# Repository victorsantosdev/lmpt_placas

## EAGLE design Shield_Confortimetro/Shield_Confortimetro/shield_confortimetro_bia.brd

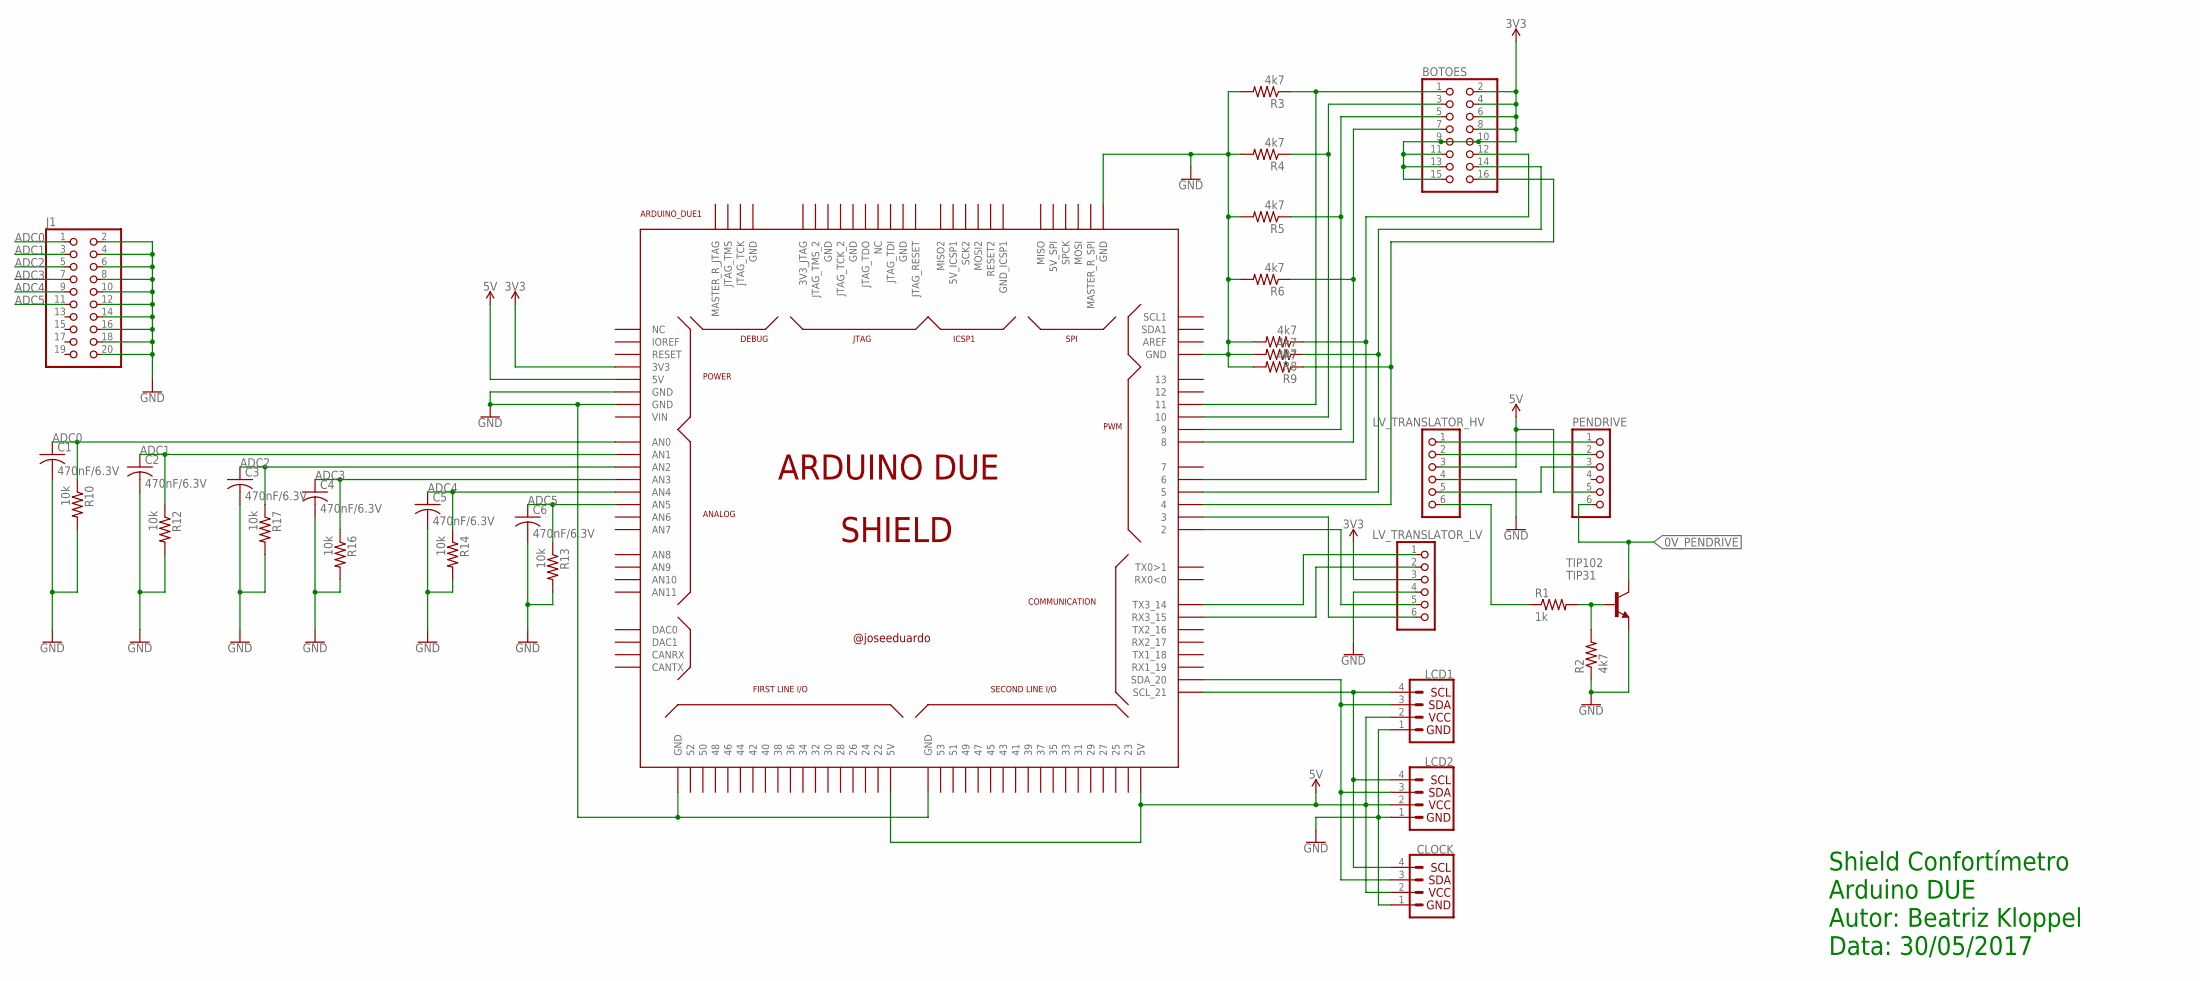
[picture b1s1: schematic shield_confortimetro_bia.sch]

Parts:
ARDUINO_DUE1: ARDUINO_DUE_SHIELD
BOTOES: PINHD-2X8; 2X08
C1, C2, C3, C4, C5, C6: 470nF/6.3V; C050-030X075
CLOCK: I2C_STANDARD; 1X04
J1: PINHD-2X10; 2X10
LCD1, LCD2: I2C_STANDARD; 1X04
LV_TRANSLATOR_HV: PINHD-1X6; 1X06
LV_TRANSLATOR_LV: PINHD-1X6; 1X06
PENDRIVE: PINHD-1X6; 1X06
R1: 1k; 0309/12
R2, R3, R4, R5, R6, R7, R8, R9: 4k7; 0309/12
R10, R12, R13, R14, R16, R17: 10k; 0309/12
TIP102: TIP31; TO220

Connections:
0V_PENDRIVE: PENDRIVE.6, TIP102.2 (C)
ADC0: ARDUINO_DUE1.A0 (AN0), C1.1, J1.1, R10.1
ADC1: ARDUINO_DUE1.A1 (AN1), C2.1, J1.3, R12.1
ADC2: ARDUINO_DUE1.A2 (AN2), C3.1, J1.5, R17.1
ADC3: ARDUINO_DUE1.A3 (AN3), C4.1, J1.7, R16.1
ADC4: ARDUINO_DUE1.A4 (AN4), C5.1, J1.9, R14.1
ADC5: ARDUINO_DUE1.A5 (AN5), C6.1, J1.11, R13.1
GND: ARDUINO_DUE1.GND, ARDUINO_DUE1.GND_1 (GND), ARDUINO_DUE1.GND_2 (GND), ARDUINO_DUE1.GND_3 (GND), ARDUINO_DUE1.GND_4 (GND), ARDUINO_DUE1.GND_5 (GND), C1.2, C2.2, C3.2, C4.2, C5.2, C6.2, CLOCK.1, J1.2, J1.4, J1.6, J1.8, J1.10, J1.12, J1.14, J1.16, J1.18, J1.20, LCD1.1, LCD2.1, LV_TRANSLATOR_HV.4, LV_TRANSLATOR_LV.4, R2.1, R3.2, R4.2, R5.2, R6.2, R7.2, R8.2, R9.2, R10.2, R12.2, R13.2, R14.2, R16.2, R17.2, TIP102.3 (E)
unnamed: ARDUINO_DUE1.20 (SDA_20), CLOCK.3, LCD1.3, LCD2.3
unnamed: ARDUINO_DUE1.21 (SCL_21), CLOCK.4, LCD1.4, LCD2.4
unnamed: ARDUINO_DUE1.14 (TX3_14), LV_TRANSLATOR_LV.1
unnamed: ARDUINO_DUE1.15 (RX3_15), LV_TRANSLATOR_LV.2
unnamed: ARDUINO_DUE1.3, LV_TRANSLATOR_LV.6
unnamed: ARDUINO_DUE1.2, LV_TRANSLATOR_LV.5
unnamed: LV_TRANSLATOR_HV.1, PENDRIVE.1
unnamed: LV_TRANSLATOR_HV.2, PENDRIVE.2
unnamed: LV_TRANSLATOR_HV.5, PENDRIVE.3
unnamed: R1.2, R2.2, TIP102.1 (B)
unnamed: LV_TRANSLATOR_HV.6, R1.1
unnamed: ARDUINO_DUE1.6, BOTOES.12, R7.1
unnamed: ARDUINO_DUE1.5, BOTOES.14, R8.1
unnamed: ARDUINO_DUE1.4, BOTOES.16, R9.1
unnamed: ARDUINO_DUE1.8, BOTOES.7, R6.1
unnamed: ARDUINO_DUE1.9, BOTOES.5, R5.1
unnamed: ARDUINO_DUE1.10, BOTOES.3, R4.1
unnamed: ARDUINO_DUE1.11, BOTOES.1, R3.1
VCC_3V3: ARDUINO_DUE1.3V3, BOTOES.2, BOTOES.4, BOTOES.6, BOTOES.8, BOTOES.9, BOTOES.10, BOTOES.11, BOTOES.13, BOTOES.15, LV_TRANSLATOR_LV.3
VCC_5V: ARDUINO_DUE1.5V0 (5V), ARDUINO_DUE1.5V0_1 (5V), ARDUINO_DUE1.5V0_2 (5V), CLOCK.2, LCD1.2, LCD2.2, LV_TRANSLATOR_HV.3, PENDRIVE.5

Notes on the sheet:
Shield Confortímetro Arduino DUE Autor: Beatriz Kloppel Data: 30/05/2017

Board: 2 copper layers, 31 parts (9 on the bottom side), 28 nets, no tracks yet.

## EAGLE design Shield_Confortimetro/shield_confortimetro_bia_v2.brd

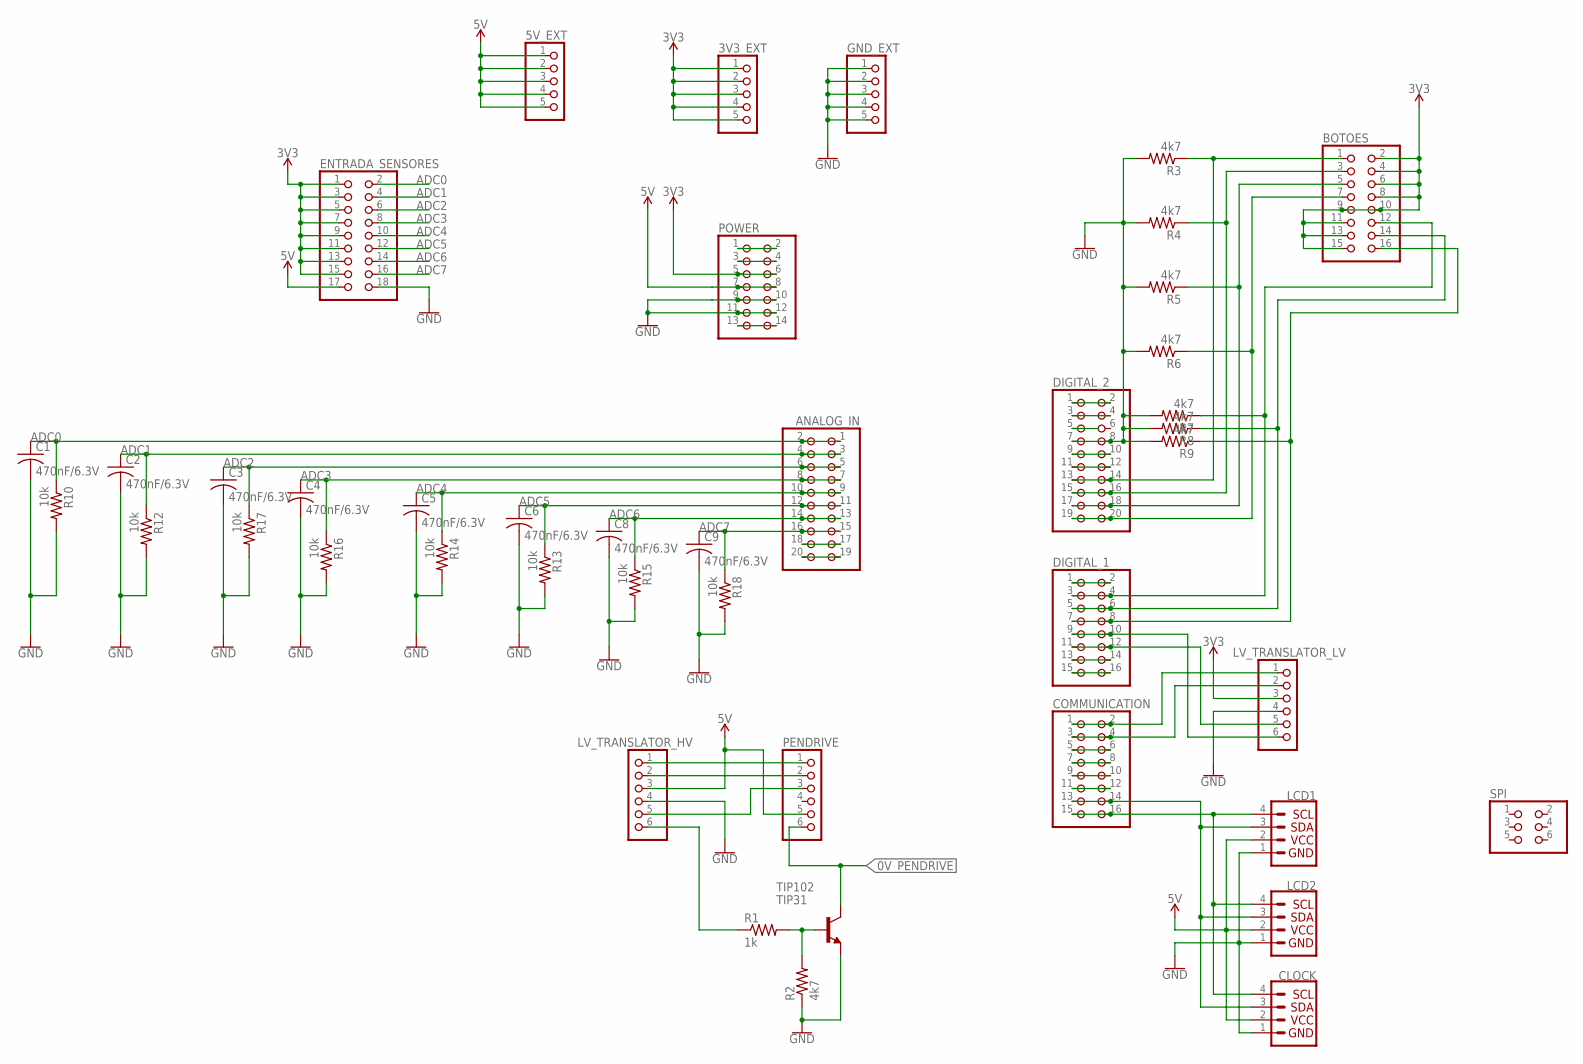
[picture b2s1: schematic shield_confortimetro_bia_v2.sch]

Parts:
3V3_EXT, 5V_EXT: PINHD-1X5; 1X05
ANALOG_IN: PINHD-2X10; 2X10
BOTOES: PINHD-2X8; 2X08
C1, C2, C3, C4, C5, C6, C8, C9: 470nF/6.3V; C050-030X075
CLOCK: I2C_STANDARD; 1X04
COMMUNICATION: PINHD-2X8; 2X08
DIGITAL_1: PINHD-2X8; 2X08
DIGITAL_2: PINHD-2X10; 2X10
ENTRADA_SENSORES: PINHD-2X9; 2X09
GND_EXT: PINHD-1X5; 1X05
LCD1, LCD2: I2C_STANDARD; 1X04
LV_TRANSLATOR_HV: PINHD-1X6; 1X06
LV_TRANSLATOR_LV: PINHD-1X6; 1X06
PENDRIVE: PINHD-1X6; 1X06
POWER: PINHD-2X7; 2X07
R1: 1k; 0309/12
R2, R3, R4, R5, R6, R7, R8, R9: 4k7; 0309/12
R10, R12, R13, R14, R15, R16, R17, R18: 10k; 0309/12
SPI: PINHD-2X3; 2X03
TIP102: TIP31; TO220

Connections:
0V_PENDRIVE: PENDRIVE.6, TIP102.2 (C)
ADC0: ANALOG_IN.1, ANALOG_IN.2, C1.1, ENTRADA_SENSORES.2, R10.1
ADC1: ANALOG_IN.3, ANALOG_IN.4, C2.1, ENTRADA_SENSORES.4, R12.1
ADC2: ANALOG_IN.5, ANALOG_IN.6, C3.1, ENTRADA_SENSORES.6, R17.1
ADC3: ANALOG_IN.7, ANALOG_IN.8, C4.1, ENTRADA_SENSORES.8, R16.1
ADC4: ANALOG_IN.9, ANALOG_IN.10, C5.1, ENTRADA_SENSORES.10, R14.1
ADC5: ANALOG_IN.11, ANALOG_IN.12, C6.1, ENTRADA_SENSORES.12, R13.1
ADC6: ANALOG_IN.13, ANALOG_IN.14, C8.1, ENTRADA_SENSORES.14, R15.1
ADC7: ANALOG_IN.15, ANALOG_IN.16, C9.1, ENTRADA_SENSORES.16, R18.1
GND: C1.2, C2.2, C3.2, C4.2, C5.2, C6.2, C8.2, C9.2, CLOCK.1, DIGITAL_2.7, DIGITAL_2.8, ENTRADA_SENSORES.18, GND_EXT.1, GND_EXT.2, GND_EXT.3, GND_EXT.4, GND_EXT.5, LCD1.1, LCD2.1, LV_TRANSLATOR_HV.4, LV_TRANSLATOR_LV.4, POWER.9, POWER.10, POWER.11, POWER.12, R2.1, R3.2, R4.2, R5.2, R6.2, R7.2, R8.2, R9.2, R10.2, R12.2, R13.2, R14.2, R15.2, R16.2, R17.2, R18.2, TIP102.3 (E)
unnamed: CLOCK.3, COMMUNICATION.13, COMMUNICATION.14, LCD1.3, LCD2.3
unnamed: CLOCK.4, COMMUNICATION.15, COMMUNICATION.16, LCD1.4, LCD2.4
unnamed: COMMUNICATION.1, COMMUNICATION.2, LV_TRANSLATOR_LV.1
unnamed: COMMUNICATION.3, COMMUNICATION.4, LV_TRANSLATOR_LV.2
unnamed: DIGITAL_1.9, DIGITAL_1.10, LV_TRANSLATOR_LV.6
unnamed: DIGITAL_1.11, DIGITAL_1.12, LV_TRANSLATOR_LV.5
unnamed: LV_TRANSLATOR_HV.1, PENDRIVE.1
unnamed: LV_TRANSLATOR_HV.2, PENDRIVE.2
unnamed: LV_TRANSLATOR_HV.5, PENDRIVE.3
unnamed: R1.2, R2.2, TIP102.1 (B)
unnamed: LV_TRANSLATOR_HV.6, R1.1
unnamed: BOTOES.12, DIGITAL_1.3, DIGITAL_1.4, R7.1
unnamed: BOTOES.14, DIGITAL_1.5, DIGITAL_1.6, R8.1
unnamed: BOTOES.16, DIGITAL_1.7, DIGITAL_1.8, R9.1
unnamed: BOTOES.7, DIGITAL_2.19, DIGITAL_2.20, R6.1
unnamed: BOTOES.5, DIGITAL_2.17, DIGITAL_2.18, R5.1
unnamed: BOTOES.3, DIGITAL_2.15, DIGITAL_2.16, R4.1
unnamed: BOTOES.1, DIGITAL_2.13, DIGITAL_2.14, R3.1
unnamed: POWER.1, POWER.2
unnamed: POWER.3, POWER.4
unnamed: POWER.13, POWER.14
unnamed: DIGITAL_2.1, DIGITAL_2.2
unnamed: DIGITAL_2.3, DIGITAL_2.4
unnamed: DIGITAL_2.9, DIGITAL_2.10
unnamed: DIGITAL_2.11, DIGITAL_2.12
unnamed: DIGITAL_1.1, DIGITAL_1.2
unnamed: DIGITAL_1.13, DIGITAL_1.14
unnamed: DIGITAL_1.15, DIGITAL_1.16
unnamed: COMMUNICATION.5, COMMUNICATION.6
unnamed: COMMUNICATION.7, COMMUNICATION.8
unnamed: COMMUNICATION.9, COMMUNICATION.10
unnamed: COMMUNICATION.11, COMMUNICATION.12
unnamed: ANALOG_IN.17, ANALOG_IN.18
unnamed: ANALOG_IN.19, ANALOG_IN.20
VCC_3V3: 3V3_EXT.1, 3V3_EXT.2, 3V3_EXT.3, 3V3_EXT.4, 3V3_EXT.5, BOTOES.2, BOTOES.4, BOTOES.6, BOTOES.8, BOTOES.9, BOTOES.10, BOTOES.11, BOTOES.13, BOTOES.15, ENTRADA_SENSORES.1, ENTRADA_SENSORES.3, ENTRADA_SENSORES.5, ENTRADA_SENSORES.7, ENTRADA_SENSORES.9, ENTRADA_SENSORES.11, ENTRADA_SENSORES.13, ENTRADA_SENSORES.15, LV_TRANSLATOR_LV.3, POWER.5, POWER.6
VCC_5V: 5V_EXT.1, 5V_EXT.2, 5V_EXT.3, 5V_EXT.4, 5V_EXT.5, CLOCK.2, ENTRADA_SENSORES.17, LCD1.2, LCD2.2, LV_TRANSLATOR_HV.3, PENDRIVE.5, POWER.7, POWER.8

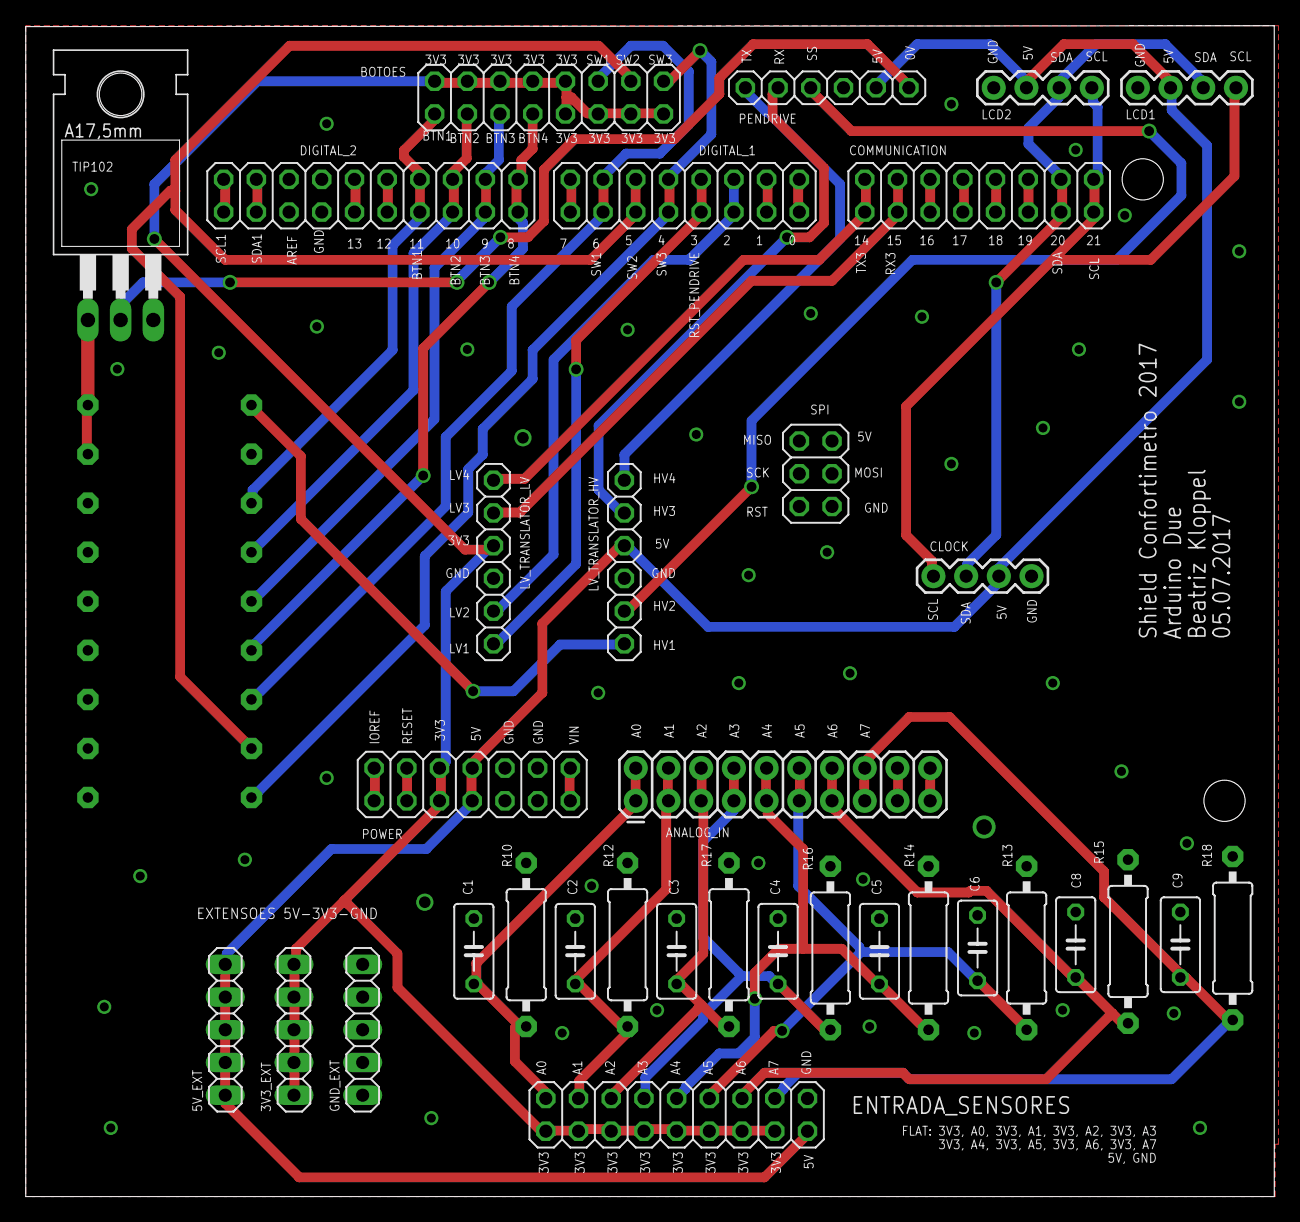
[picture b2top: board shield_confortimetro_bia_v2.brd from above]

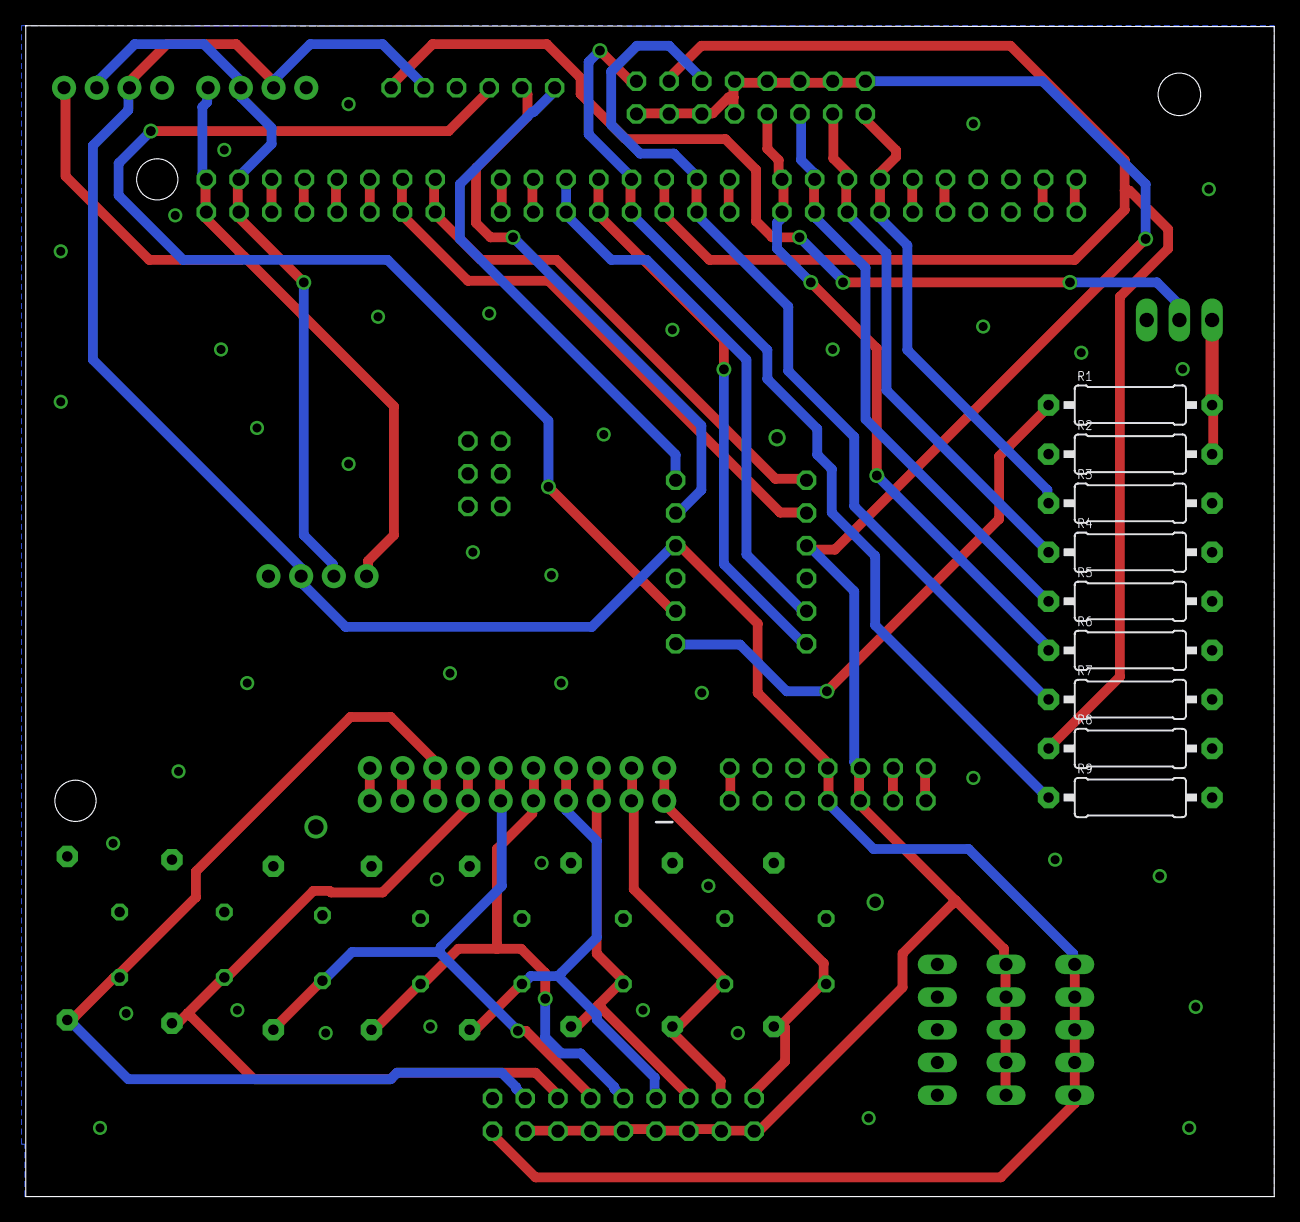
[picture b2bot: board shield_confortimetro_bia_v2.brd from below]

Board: 2 copper layers, 97.0 x 90.9 mm, 43 parts (9 on the bottom side), 46 nets.

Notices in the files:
parts and their libraries:
SparkFun-Connectors: Licensing: Creative Commons ShareAlike 4.0 International - https://creativecommons.org/licenses/by-sa/4.0
